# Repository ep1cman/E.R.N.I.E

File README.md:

About
=====

A few years ago [EARS](https://twitter.com/surreyears?lang=en) were asked by the University of Surrey to create a project for an event called [Headstart](http://www.etrust.org.uk/headstart/courses). During this week long event a group of sixth form students who are considering studying engineering at university have around 5 hours of lab sessions to complete a project.

E.R.N.I.E (EARS Robotic Navigator and Intrepid Explorer) was the project I came up with for the electronic engineering project. ERNIE is a very low cost line following robot that can be assembled and programmed by students with very little previous knowledge in electronics or programming.

Over the past few years the project has evolved to become (almost) fully re-usable by only requiring zip ties, screws and electrical tape to assemble. The only part that cannot be done again is the soldering of the PCB, but the assembled PCB can of course be re-used.

Notes for schools and people making their own
=============================================
Assembly instructions for building an E.R.N.I.E can be found [here](doc/assembly instructions.pdf).
While these are mostly complete they assume you have been given a ready made kit and don't include preparation details.
Additional notes for schools can be found [here](SCHOOLS.md).

If you are an individual wanting to make an E.R.N.I.E for yourself please read through the [kit preparation](SCHOOLS.md#kit-preparation) section on the schools page for details on the extra steps you will need to take. For individuals I can also offer free PCBs since I have quite a lot left over. All I ask is you cover the postage costs (won't be much because it can be sent as a small letter). Just drop me an email at sebastian.goscik@live.co.uk

Code examples
=============
Code examples for E.R.N.I.E are kept in a separate repository that can be found [here]()

Files
=====
 * __/BoM.pdf__ - Bill of Materials, contains a complete list of parts needed and where to buy them
 * __/Chassis v2.1.dxf__ - Chassis design for a laser cutter
 * __/Chassis v2.1.razorlab.svg__ - Same as above but ready to be sent straight to [Razorlab](http://razorlab.co.uk/) using their P1 size
 * __/README.md__ - This is the file you are now reading
 * __/SCHOOLS.md__ - Information on using E.R.N.I.E in schools e.g. kit preparation details
 * __/doc/assembly instructions.pdf__ - Instructions on how to assemble E.R.N.I.E (including diagrams)
 * __/doc/worksheet.pdf__ - Basic arduino and line following tutorial
 * __/doc/Sensor board - XXX.pdf__ - Schematic and PCB files in viewable form
 * __/license/XXX__ - Details about how this project is licensed, including who to email when you make changes or a production run
 * __/PCB/XXX__ - [Cadsoft EAGLE](http://www.cadsoftusa.com/) source files for the sensor board
 * __/src/3d/XXX__ - Autodesk Inventor source files that this project was made from
 * __/src/doc/XXX__ - Microsoft Word source files for the assembly instructions and worksheet
 * __/src/PCB/XXX__ - Cadsoft EAGLE source file for a panellised version of the pcb and the one used in the pcb pdf
 * __/src/PCB/gerbers (elecrow).zip__ - The gerber files sent to [Elecrow](http://www.elecrow.com/) to produce the PCBs
 * __/src/BoM.xlsx - Microsoft Excel source for the bill of materials

To Do
=====
There are a few extra things I would like to add to this project in the future if time permits:
 * 3D printed shroud for the IR sensors to minimise cross talk
 * 3D printed servo -> HC-SR04 mount
 * Add soldering instructions
 * add software setup instructions

If you manage to implement any of the above or something I haven't even considered please let me know!

Credit
======
The very first version of the E.R.N.I.E chassis was created with the help of my good friend [Revanth Adiga](https://uk.linkedin.com/pub/revanth-adiga/a7/94a/929)

CAD models used:
 * [Arduino by Andrew Whitham](https://grabcad.com/library/arduino-uno-r3-1)
 * [Motor Shield by mandrillon](https://grabcad.com/library/adafruit-motor-shield-v2-1)
 * [Battery Holder by Georgina Koffler](https://grabcad.com/library/6-aa-battery-pack)
 * [AA Battery by Cody Thurston](https://grabcad.com/library/energizer-aa-battery)

License
=======
Copyright S.Goscik 2015

The schematic, PCB and chassis designs and their respective documentation are Open Hardware and are licensed under the CERN OHL v. 1.2.
You may redistribute and modify this work under the terms of the CERN OHL v.1.2. (http://ohwr.org/cernohl). This work is distributed WITHOUT ANY EXPRESS OR IMPLIED WARRANTY, INCLUDING OF MERCHANTABILITY, SATISFACTORY QUALITY AND FITNESS FOR A PARTICULAR PURPOSE. Please see the CERN OHL v.1.2 for applicable conditions

There are only a few simple requirement that you must do under this license:

 * If you make any changes to the project please share them freely, under the same license.
 * Please list your changes in [CHANGES.TXT](license/CHANGES.TXT).
 * Please notify the people listed in [CONTRIB.TXT](license/CONTRIB.TXT) of your changes.
 * If you know how to use git and feel your change improve the project (e.g. fixing my spelling/grammar or updating the worksheet) please fork this repository and make a pull request of your changes.
 * If you produce any E.R.N.I.E kits (chassis or PCBs) please notify the people listed in [PRODUCT.TXT](license/PRODUCT.TXT).

If any of your e-mails fail to go through you don't need to worry about it. The reason I ask for these things is so that the people who have contributed to the project can see how it progresses and that it remains free for everyone.

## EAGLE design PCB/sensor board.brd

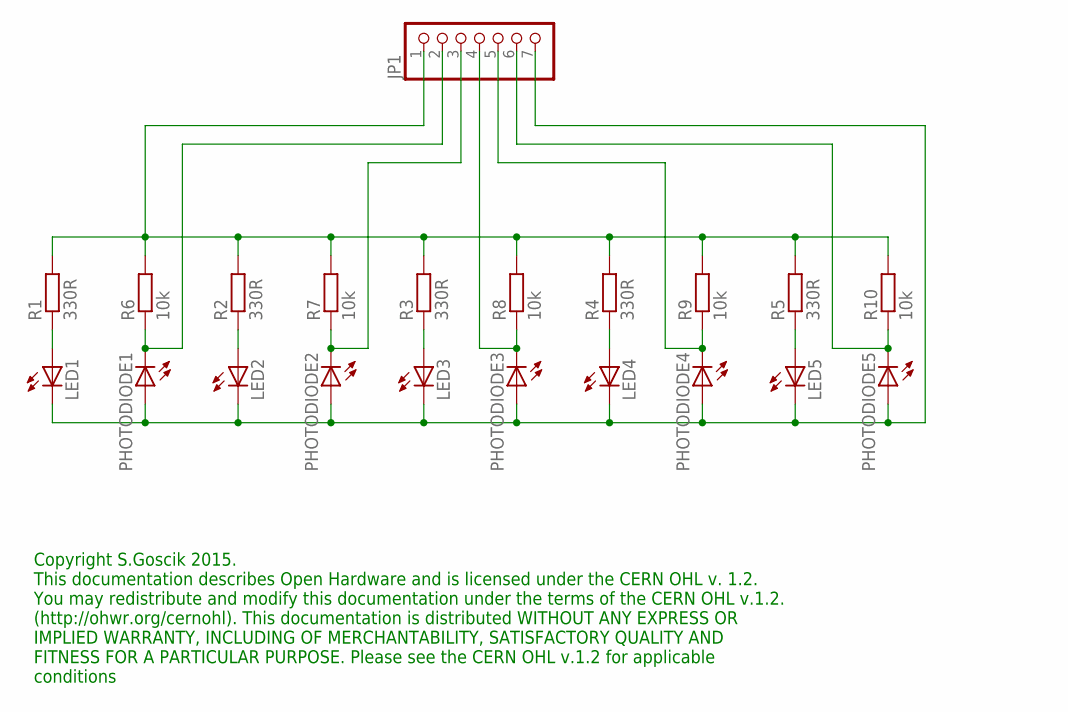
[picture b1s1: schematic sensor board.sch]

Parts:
JP1: PINHD-1X7; 1X07
LED1, LED2, LED3, LED4, LED5: LED3MM
PHOTODIODE1, PHOTODIODE2, PHOTODIODE3, PHOTODIODE4, PHOTODIODE5: LED3MM
R1, R2, R3, R4, R5: 330R; 0207/10
R6, R7, R8, R9, R10: 10k; 0207/10

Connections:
unnamed: LED1.A, R1.1
unnamed: LED2.A, R2.1
unnamed: JP1.3, PHOTODIODE2.K (C), R7.1
unnamed: LED3.A, R3.1
unnamed: JP1.4, PHOTODIODE3.K (C), R8.1
unnamed: LED4.A, R4.1
unnamed: JP1.5, PHOTODIODE4.K (C), R9.1
unnamed: LED5.A, R5.1
unnamed: JP1.6, PHOTODIODE5.K (C), R10.1
unnamed: JP1.1, R1.2, R2.2, R3.2, R4.2, R5.2, R6.2, R7.2, R8.2, R9.2, R10.2
unnamed: JP1.7, LED1.K (C), LED2.K (C), LED3.K (C), LED4.K (C), LED5.K (C), PHOTODIODE1.A, PHOTODIODE2.A, PHOTODIODE3.A, PHOTODIODE4.A, PHOTODIODE5.A
unnamed: JP1.2, PHOTODIODE1.K (C), R6.1

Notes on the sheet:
Copyright S.Goscik 2015. This documentation describes Open Hardware and is licensed under the CERN OHL v. 1.2. You may redistribute and modify this documentation under the terms of the CERN OHL v.1.2. (http://ohwr.org/cernohl). This documentation is distributed WITHOUT ANY EXPRESS OR IMPLIED WARRAN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

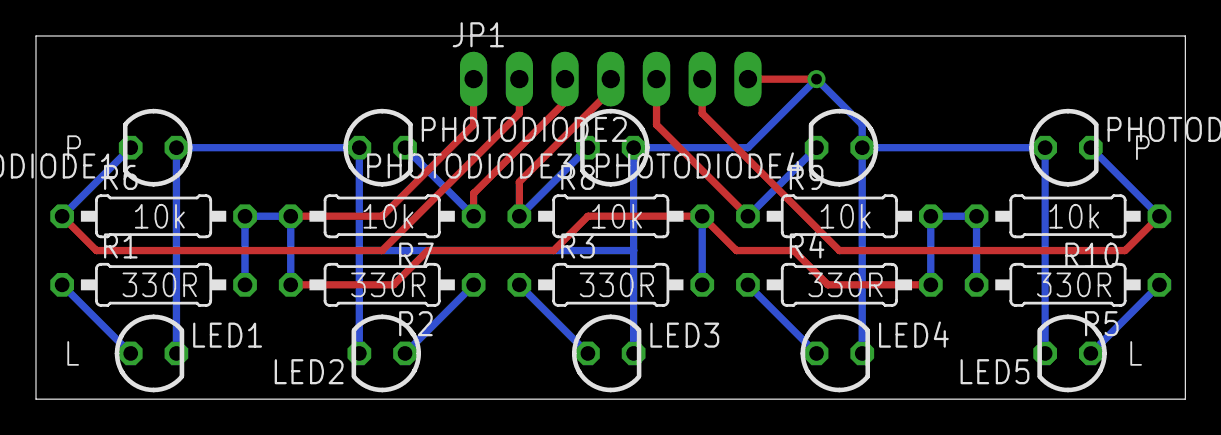
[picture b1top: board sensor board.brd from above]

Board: 2 copper layers, 63.9 x 20.2 mm, 21 parts (0 on the bottom side), 12 nets.

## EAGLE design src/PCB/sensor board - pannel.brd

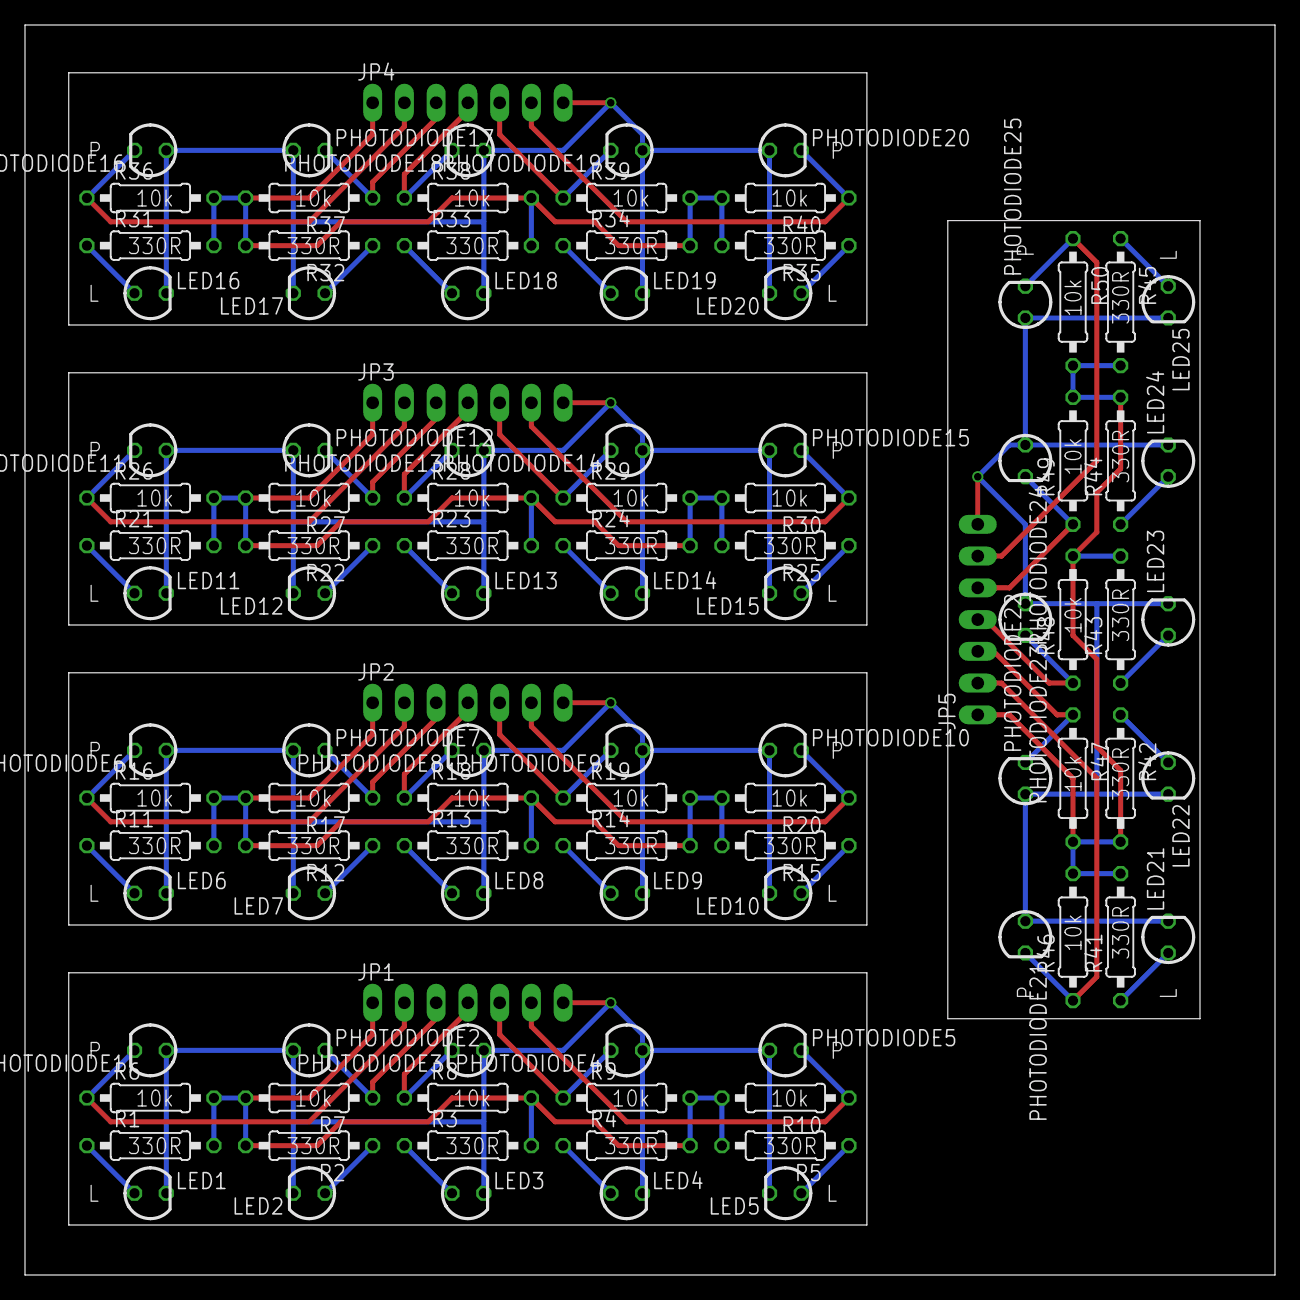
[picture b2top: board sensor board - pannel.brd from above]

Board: 4 copper layers, 100.0 x 100.0 mm, 105 parts (0 on the bottom side), 60 nets.

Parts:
JP1, JP2, JP3, JP4, JP5: 1X07
LED1, LED2, LED3, LED4, LED5, LED6, LED7, LED8, LED9, LED10, LED11, LED12, LED13, LED14, LED15, LED16, LED17, LED18, LED19, LED20, LED21, LED22, LED23, LED24, LED25: LED3MM
PHOTODIODE1, PHOTODIODE2, PHOTODIODE3, PHOTODIODE4, PHOTODIODE5, PHOTODIODE6, PHOTODIODE7, PHOTODIODE8, PHOTODIODE9, PHOTODIODE10, PHOTODIODE11, PHOTODIODE12, PHOTODIODE13, PHOTODIODE14, PHOTODIODE15, PHOTODIODE16, PHOTODIODE17, PHOTODIODE18, PHOTODIODE19, PHOTODIODE20, PHOTODIODE21, PHOTODIODE22, PHOTODIODE23, PHOTODIODE24, PHOTODIODE25: LED3MM
R1, R2, R3, R4, R5, R6, R7, R8, R9, R10, R11, R12, R13, R14, R15, R16, R17, R18, R19, R20, R21, R22, R23, R24, R25, R26, R27, R28, R29, R30, R31, R32, R33, R34, R35, R36, R37, R38, R39, R40, R41, R42, R43, R44, R45, R46, R47, R48, R49, R50: 0207/10

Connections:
unnamed: LED1.A, R1.1
unnamed: LED6.A, R11.1
unnamed: LED2.A, R2.1
unnamed: JP1.3, PHOTODIODE2.K, R7.1
unnamed: LED3.A, R3.1
unnamed: JP1.4, PHOTODIODE3.K, R8.1
unnamed: LED4.A, R4.1
unnamed: JP1.5, PHOTODIODE4.K, R9.1
unnamed: LED5.A, R5.1
unnamed: JP1.6, PHOTODIODE5.K, R10.1
unnamed: JP1.1, R1.2, R2.2, R3.2, R4.2, R5.2, R6.2, R7.2, R8.2, R9.2, R10.2
unnamed: JP1.7, LED1.K, LED2.K, LED3.K, LED4.K, LED5.K, PHOTODIODE1.A, PHOTODIODE2.A, PHOTODIODE3.A, PHOTODIODE4.A, PHOTODIODE5.A
unnamed: JP1.2, PHOTODIODE1.K, R6.1
unnamed: LED7.A, R12.1
unnamed: JP2.3, PHOTODIODE7.K, R17.1
unnamed: LED8.A, R13.1
unnamed: JP2.4, PHOTODIODE8.K, R18.1
unnamed: LED9.A, R14.1
unnamed: JP2.5, PHOTODIODE9.K, R19.1
unnamed: LED10.A, R15.1
unnamed: JP2.6, PHOTODIODE10.K, R20.1
unnamed: JP2.1, R11.2, R12.2, R13.2, R14.2, R15.2, R16.2, R17.2, R18.2, R19.2, R20.2
unnamed: JP2.7, LED6.K, LED7.K, LED8.K, LED9.K, LED10.K, PHOTODIODE6.A, PHOTODIODE7.A, PHOTODIODE8.A, PHOTODIODE9.A, PHOTODIODE10.A
unnamed: JP2.2, PHOTODIODE6.K, R16.1
unnamed: LED11.A, R21.1
unnamed: LED12.A, R22.1
unnamed: JP3.3, PHOTODIODE12.K, R27.1
unnamed: LED13.A, R23.1
unnamed: JP3.4, PHOTODIODE13.K, R28.1
unnamed: LED14.A, R24.1
unnamed: JP3.5, PHOTODIODE14.K, R29.1
unnamed: LED15.A, R25.1
unnamed: JP3.6, PHOTODIODE15.K, R30.1
unnamed: JP3.1, R21.2, R22.2, R23.2, R24.2, R25.2, R26.2, R27.2, R28.2, R29.2, R30.2
unnamed: JP3.7, LED11.K, LED12.K, LED13.K, LED14.K, LED15.K, PHOTODIODE11.A, PHOTODIODE12.A, PHOTODIODE13.A, PHOTODIODE14.A, PHOTODIODE15.A
unnamed: JP3.2, PHOTODIODE11.K, R26.1
unnamed: LED16.A, R31.1
unnamed: LED17.A, R32.1
unnamed: JP4.3, PHOTODIODE17.K, R37.1
unnamed: LED18.A, R33.1
unnamed: JP4.4, PHOTODIODE18.K, R38.1
unnamed: LED19.A, R34.1
unnamed: JP4.5, PHOTODIODE19.K, R39.1
unnamed: LED20.A, R35.1
unnamed: JP4.6, PHOTODIODE20.K, R40.1
unnamed: JP4.1, R31.2, R32.2, R33.2, R34.2, R35.2, R36.2, R37.2, R38.2, R39.2, R40.2
unnamed: JP4.7, LED16.K, LED17.K, LED18.K, LED19.K, LED20.K, PHOTODIODE16.A, PHOTODIODE17.A, PHOTODIODE18.A, PHOTODIODE19.A, PHOTODIODE20.A
unnamed: JP4.2, PHOTODIODE16.K, R36.1
unnamed: LED21.A, R41.1
unnamed: LED22.A, R42.1
unnamed: JP5.3, PHOTODIODE22.K, R47.1
unnamed: LED23.A, R43.1
unnamed: JP5.4, PHOTODIODE23.K, R48.1
unnamed: LED24.A, R44.1
unnamed: JP5.5, PHOTODIODE24.K, R49.1
unnamed: LED25.A, R45.1
unnamed: JP5.6, PHOTODIODE25.K, R50.1
unnamed: JP5.1, R41.2, R42.2, R43.2, R44.2, R45.2, R46.2, R47.2, R48.2, R49.2, R50.2
unnamed: JP5.7, LED21.K, LED22.K, LED23.K, LED24.K, LED25.K, PHOTODIODE21.A, PHOTODIODE22.A, PHOTODIODE23.A, PHOTODIODE24.A, PHOTODIODE25.A
unnamed: JP5.2, PHOTODIODE21.K, R46.1

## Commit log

2015-09-30 Initial release
    The initial public release of E.R.N.I.E
2018-09-19 Fixes
    Fixed broken links and removed a temp file

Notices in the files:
PCB/sensor board.brd:
Licensed under CERN OHL v.1.2
